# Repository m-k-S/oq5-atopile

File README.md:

# openquantumv5

control board

Created by max <pepper@atopile.io>

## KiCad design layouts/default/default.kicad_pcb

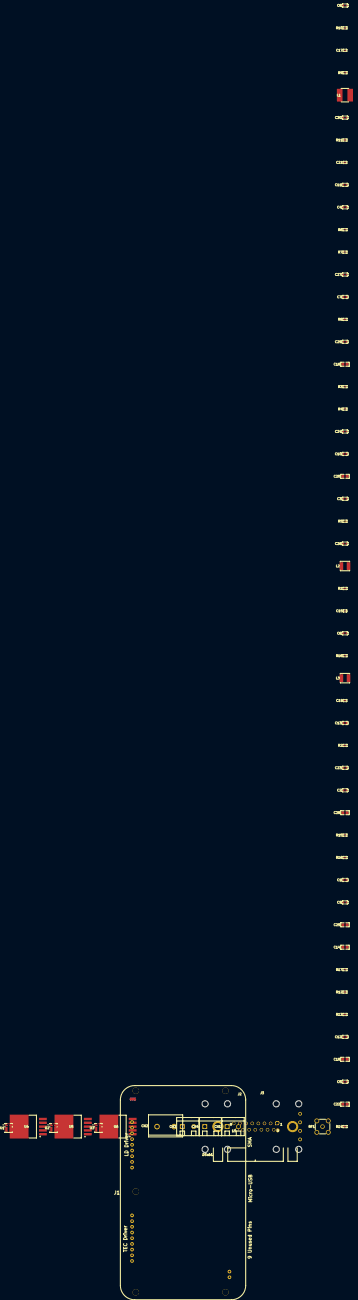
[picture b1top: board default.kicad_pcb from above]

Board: 2 copper layers, 66 parts (0 on the bottom side), 32 nets, no tracks yet.

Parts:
C1, C2, C3, C4, C5, C6, C7, C8, C9, C10, C11, C12, C13, C23, C24, C26, C27, C29, C30: 100nF; C0603
C14, C16, C18, C20, C22, C25, C28: 10µF; C0805
C15, C17, C19, C21: 100nF; C0402
CN1, CN3, CN4: CONN-TH_2P-P5.08_1729128
CN2: CONN-TH_2P-P7.62_1717729
DSub1: DSUB-TH_15P-P2.74-S2.84_L18.5-W39.1-M
J1: TsKoheronModel_ViasandDrillHolesFootprint-Footprint-1
J2: RFENABLE
J3: VTUNE
L1: L 470µH; IND-SMD_L6.0-W6.0_FNR60XXS
L2, L3: L 10µH; IND-SMD_L4.0-W4.0
R1, R2, R4, R5, R7, R8, R10, R11, R13, R14, R16, R17: 10kΩ; R0402
R3: 133kΩ; R0402
R6, R9: 107kΩ; R0402
R12: 46.4kΩ; R0402
R15, R18: 30kΩ; R0402
RF1: SMA-TH_BWSMA-KE-Z001
U1, U2, U3: QFN-7_L4.0-W3.3_TPSM863257RDXR
U4, U5, U6: D2PAK-5_L10.0-W9.2-P1.70-LS14.5-BR

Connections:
Adj: R11.1, R12.2, U4.5
EN: R1.2, U1.6
Enable: R10.2, U4.1
FB: R2.1, R3.2, U1.7
buck_redpitaya-FB: R5.1, R6.2, U2.7
buck_redpitaya-enable-EN: R4.2, U2.6
buck_vco-FB: R8.1, R9.2, U3.7
buck_vco-enable-EN: R7.2, U3.6
filter_5v_rp-power_out-hv: C16.1, C17.1, CN1.1, L2.2
filter_15v-power_in-hv: C18.1, C19.1, CN2.1, L3.1
filter_15v-power_out-hv: C20.1, C21.1, CN3.1, CN4.1, L3.2, R1.1, R4.1, R7.1, U1.1, U2.1, U3.1
hv: C1.1, RF1.1
ld_n: DSub1.9, J1.LD-
ld_p: DSub1.1, J1.LD+
ldo_7v-power_in-hv: C22.1, R3.1, R10.1, U1.3, U4.2
ldo_7v-power_out-hv: J1.VS, R12.1, U4.4
ldo_redpitaya-Adj: R14.1, R15.2, U5.5
ldo_redpitaya-enable-Enable: R13.2, U5.1
ldo_redpitaya-power_in-hv: C25.1, R6.1, R13.1, U2.3, U5.2
ldo_redpitaya-power_out-hv: C14.1, C15.1, L2.1, R15.1, U5.4
ldo_vco-Adj: R17.1, R18.2, U6.5
ldo_vco-enable-Enable: R16.2, U6.1
ldo_vco-power_in-hv: C28.1, R9.1, R16.1, U3.3, U6.2
ldo_vco-power_out-hv: DSub1.7, R18.1, U6.4
lv: C1.2, DSub1.8, L1.2
pelt_n: DSub1.2, J1.TEC-1, J1.TEC-2
pelt_p: DSub1.3, J1.TEC+1, J1.TEC+2
reference-lv: C14.2, C15.2, C16.2, C17.2, C18.2, C19.2, C20.2, C21.2, C22.2, C25.2, C28.2, CN1.2, CN2.2, CN3.2, CN4.2, DSub1.0, J1.GND1, J1.GND2, J1.GND3, J1.GND4, J1.GND5, J1.GND6, J1.GND7, J2.2, J3.4, R2.2, R5.2, R8.2, R11.2, R14.2, R17.2, RF1.2, RF1.3, RF1.4, RF1.5, U1.4, U2.4, U3.4, U4.3, U4.6, U5.3, U5.6, U6.3, U6.6
rf_enable: DSub1.15, J2.1
th_n: DSub1.5, J1.TH-
th_p: DSub1.4, J1.TH+
vtune: J3.3, L1.1

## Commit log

2026-03-24 test
2026-03-25 more connectors
2026-03-25 adding phidgets boards
2026-03-25 changing signals a bit
2026-03-25 adding more filtering
2026-03-26 fixing dps5005 connections
